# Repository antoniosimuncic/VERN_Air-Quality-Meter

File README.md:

# VERN' University  
Internet of Things Department  
Professor: doc. dr. sc. Petar Kolar, Roman Rubčić, dipl. ing. graf. teh.  
Student: Antonio Šimunčić  

**Smart air quality monitor**  

Zagreb, Croatia  
November, 2024  

# Introduction to the Smart Air Quality Monitor Project

Air pollution is becoming an increasingly serious environmental and health issue, affecting people's quality of life worldwide. Harmful particles and gases in the atmosphere can lead to numerous health problems, making air quality monitoring essential for protecting health and the environment.

The goal of this project is to develop a Smart Air Quality Monitor, a smart meteorological station that integrates advanced sensors to measure airborne dust particles, CO2, humidity, pressure, and temperature. This device would enable real-time air quality monitoring, providing users with critical information to help them make informed decisions and take necessary precautions.

# Week 1 - System architecture

Project Requirements:  

- **Temperature and Humidity Measurement**
- **Dust Particle Measurement** (PM1, PM2.5, PM4, PM10)
- **VOC Index Measurement** (Volatile Organic Compounds)
- **CO2 Level Measurement** in the Air
- **Atmospheric Pressure Measurement**
- **User Data Display**
- **Wireless Network Connectivity**

After defining the device requirements, I began searching for suitable components on platforms like Mouser, TME, and Aliexpress to find those that best match the specifications. The goal was to select reliable components that ensure high accuracy and longevity of the system, while also being compatible with the microcontroller and its software support.

For the microcontroller, I chose the ESP32-S3-WROOM-1 (N16R8) due to its affordable price, dual-core processor, ample onboard flash memory (16MB), and integrated PSRAM (8MB), which serves as a frame buffer for generating the graphical interface. Additionally, the microcontroller module includes built-in Wi-Fi and Bluetooth RF interfaces and an antenna, which significantly shortens development time and reduces the risk of wireless communication issues. 

**Block diagram:**  

# Week 2 - Schematic drawing

In week 2, I began creating the schematic in KiCad. The first task was to place all the selected components in the schematic, followed by a detailed study of the datasheets for the chosen components to ensure correct connections and desired system functionality. At this stage, I am also working on optimizing the schematic and the Bill of Materials (BOM) for a smooth transition to PCB design later on.

# Week 3 - Schematic release

In week 3, I completed the schematic design and released the finalized version. This involved thoroughly verifying all component connections and ensuring compatibility across the system, focusing on power distribution, signal integrity, and communication pathways between components. After careful checks, I created a preliminary Bill of Materials (BOM) and added detailed annotations to the schematic to guide the upcoming PCB layout phase. The release of the schematic marks a significant milestone, setting the foundation for the PCB design and allowing for initial testing.

**Schematic:** [Revision 10](https://github.com/antoniosimuncic/VERN_Air-Quality-Meter/blob/main/Hardware/100008_hw-vern-aqm/Schematic/100008_hw-vern-aqm.pdf)

# Week 4 - PCB design

In the fourth week of the project, I began designing the PCB based on the finalized schematic. This phase involved selecting the appropriate board dimensions, component placement, and routing the connections while considering design rules such as trace width, clearance, and power and heat management. A key focus was on USB differential pair impedance control, ensuring that the USB signal traces were routed with the correct 90Ω differential impedance to maintain signal integrity and reliable data transfer. I also worked on optimizing the layout for signal integrity, minimizing the length of high-speed signal traces, and ensuring proper reference planes and return paths for the components. After completing the layout and routing, I performed a Design Rule Check (DRC) to identify and correct any potential issues before moving on to generating the Gerber files for fabrication.

**PCB render:**  

# Week 5 - Component procurement  

In week 5, I focused on component procurement and ordering essential parts to prepare for assembly. I purchased components from Mouser to ensure the reliability of critical parts while sourcing additional items from Aliexpress for cost-effectiveness. Additionally, I ordered the PCBs and a stencil for solder application from JLCPCB. With components and PCBs on the way, the project is set to progress smoothly into the assembly phase once all parts arrive.

[Bill of Materials](https://html-preview.github.io/?url=https://github.com/antoniosimuncic/VERN_Air-Quality-Meter/blob/main/Hardware/100008_hw-vern-aqm/Manufacturing/Assembly/ibom/ibom.html)  

[Project expense report](https://github.com/antoniosimuncic/VERN_Air-Quality-Meter/blob/main/Documentation/project-expense-report.md)  

# Week 6 - PCB Assembly  

In week 6, I began assembling the PCB as the components and boards had arrived. Using the stencil from JLCPCB, I applied solder paste to the pads, and then I carefully placed each component onto the board, paying special attention to orientation and alignment. After assembling the board, I placed the board on an SMD hotplate reflow soldering station to perform the reflow soldering process. After the board cooled down, I inspected the connections to ensure the soldering process finished successfully. With the PCB assembly complete, I began the first board power-up to do the initial testing and troubleshooting.  

**Production process:**  

# Week 7 - Board Bring-Up  

In week 7, I focused on the initial bring-up of the PCB. After assembling the board, I verified the power rails and ensured all components received the correct voltages. Basic functionality, including communication interfaces such as UART and I2C, was tested to confirm proper connectivity between the microcontroller and peripherals. Rigol DS1054z oscilloscope was used to identify and resolve minor issues on the UART lines. Soldering fixes were necessary to ensure the board operated as expected. This stage established a solid foundation for further firmware development and system testing.  

**Sensor test source code:** [sensors-bring-up.cpp](https://github.com/antoniosimuncic/VERN_Air-Quality-Meter/blob/main/Documentation/sensors-bring-up.cpp)  

# Week 8 - Case design  

In week 8, I focused on designing a custom 3D-printed case for the device after I had confirmed the board functioned as expected. The design accounted for component placement, ventilation, and accessibility for ports and connectors. Aesthetics and durability were considered to ensure the case complemented the functionality and appearance of the project. This step helped prepare the device for practical use and testing in real-world conditions. The 3D print was made using PET-G on the BambuLab P1S printer.  

**Case design:**  

# Week 9: Firmware Architecture and Server Communication

In week 9, the focus was on developing and refining the firmware responsible for Wi-Fi connectivity, data acquisition, and communication with an HTTP server. Below is a detailed breakdown of the tasks completed and code implementations.

### Wi-Fi Connectivity

The firmware establishes a Wi-Fi connection using the ESP32-S3 microcontroller. A robust retry mechanism was implemented to handle connection failures.

**Code Snippet**:
```c
void connectToWifi() {
    uint8_t attempt = 0;
    while (attempt < WIFI_RETRIES) {
        Serial.printf("Attempt %u to connect to Wi-Fi...\n", attempt++);
        WiFi.mode(WIFI_STA);
        WiFi.begin(SECRET_SSID, SECRET_PASSWORD);
        unsigned long startAttemptTime = millis();
        while (WiFi.status() != WL_CONNECTED && millis() - startAttemptTime < WIFI_TIMEOUT) {
            delay(10);
            yield();
        }
        if (WiFi.status() == WL_CONNECTED) {
            Serial.println("Connected to Wi-Fi");
            Serial.print("IP Address: ");
            Serial.println(WiFi.localIP());
            return;
        }
        Serial.println("Failed to connect. Retrying...");
        delay(2000);
        attempt++;
    }
    Serial.println("Exceeded maximum retry attempts. Check your Wi-Fi credentials or network.");
}
```

### Server Communication

Data collected from sensors is sent to an HTTP server in JSON format. The sendDataToHTTPServer function handles this process, including constructing the JSON payload and managing HTTP requests.

**Request body:**
```json
{
 "mac_address": "AA:BB:CC:DD:EE:FF",
 "temperature": 22.5,
 "humidity": 45.0,
 "pm1": 10,
 "pm2_5": 20,
 "pm4": 25,
 "pm10": 30,
 "co2": 450,
 "voc": 100,
 "pressure": 1013.25
}
```
     
**Code Snippet:**
```c
void sendDataToHTTPServer(String mac_address, float temperature, float humidity, float pm1, float pm2_5, float pm4, float pm10, uint16_t co2, float voc, float pressure) {
    String jsonData = "{";
    jsonData += "\"mac_address\":\"" + mac_address + "\",";
    jsonData += "\"temperature\":" + String(temperature) + ",";
    jsonData += "\"humidity\":" + String(humidity) + ",";
    jsonData += "\"pm1\":" + String(pm1) + ",";
    jsonData += "\"pm2_5\":" + String(pm2_5) + ",";
    jsonData += "\"pm4\":" + String(pm4) + ",";
    jsonData += "\"pm10\":" + String(pm10) + ",";
    jsonData += "\"co2\":" + String(co2) + ",";
    jsonData += "\"voc\":" + String(voc) + ",";
    jsonData += "\"pressure\":" + String(pressure);
    jsonData += "}";

    if (WiFi.status() == WL_CONNECTED) {
        HTTPClient http;
        http.begin(SERVER_URL);
        http.addHeader("Content-Type", "application/json");
        int httpResponseCode = http.POST(jsonData);
        if (httpResponseCode > 0) {
            String response = http.getString();
            Serial.println("Response code: " + String(httpResponseCode));
            Serial.println("Response: " + response);
        } else {
            Serial.println("Error on sending POST: " + String(httpResponseCode));
        }
        http.end();
    } else {
        Serial.println("Wi-Fi not connected");
    }
}
```
**View Full Code:** [server_functions.cpp](https://github.com/antoniosimuncic/VERN_Air-Quality-Meter/blob/main/Software/100009-fw-vern-aqm/lib/server_functions/server_functions.cpp)

# Week 10: LCD Integration and Sensor Visualization

In week 10, the focus shifted to integrating the TFT display for visualizing sensor data. The firmware includes functionality for determining display colors based on sensor values, enhancing user experience.

### Dynamic Value Coloring

Each sensor value is displayed in a color-coded format to indicate its status (e.g., good, mediocre, bad, terrible).  
Functions like `getTempColor()` and `getHumidityColor()` determine the appropriate color for each value.

**Code Snippet:**
```c
uint16_t getHumidityColor(float humidity) {

    uint8_t targetHumidity = 50;
    if (abs(targetHumidity-humidity) <= 10) {
        return GOOD_COLOR;  // Green for humidity 40-60%
    } else if (abs(targetHumidity-humidity) <= 15) {
        return MEDIOCRE_COLOR;  // Yellow for humidity 35-65%
    } else if (abs(targetHumidity-humidity) <= 20) {
        return BAD_COLOR;  // Orange for humidity 30-70%
    } else {
        return TERRIBLE_COLOR;  // Red for humidity under 30 or over 70%
    }
}
```
**View Full Code:** [lcd_functions.cpp](https://github.com/antoniosimuncic/VERN_Air-Quality-Meter/blob/main/Software/100009-fw-vern-aqm/lib/lcd_functions/lcd_functions.cpp)

### Sensor Value Visualization

The display shows sensor values for temperature, humidity, CO2, VOC Index, and particulate matter (PM1, PM2.5, PM10). Each value is updated dynamically and rendered in real time.

**Code Snippet:**
```c
// Draw initial UI with Wi-Fi credentials
void drawUI() {
    sprite.fillSprite(BACKGROUND_COLOR);

    drawClockAndWiFi();

    sprite.setTextDatum(TL_DATUM); // Top-left
    sprite.setTextColor(TEXT_COLOR, TOP_BAR_COLOR);
    sprite.setTextSize(3);
    sprite.drawString("Time Zone", 10, 8);
    sprite.setTextDatum(TL_DATUM); // Top-left
    sprite.setTextColor(TEXT_COLOR, BACKGROUND_COLOR);
    sprite.setTextSize(3);
    sprite.drawString("SSID:", 20, 60);  sprite.drawString(SECRET_SSID, 120, 60);
    sprite.drawString("PASS:", 20, 120); sprite.drawString(SECRET_PASSWORD, 120, 120);
    sprite.drawString("IP:", 20, 180); sprite.drawString(ipString, 120, 180);

    sprite.pushSprite(0, 0);
    sprite.fillRect(0,35,480,285, BACKGROUND_COLOR);
    sprite.pushSprite(0, 0);

}

// Draw widgets with specified values
void drawWidget(int x, int y, int w, int h, const char* label, const char* unit, const char* value, uint16_t color) {
    // Draw the rounded rectangle
    sprite.fillRoundRect(x, y, w, h, 10, color);
    sprite.fillRoundRect(x + 5, y + 5, w - 10, h - 10, 5, BACKGROUND_COLOR);

    // Draw the label
    sprite.setTextColor(TEXT_COLOR, BACKGROUND_COLOR);
    sprite.setTextDatum(TC_DATUM);
    sprite.setTextSize(2);
    sprite.drawString(label, x + w / 2, y + 12);

    // Draw the value
    sprite.setTextSize(2);
    sprite.setTextColor(MEASUREMENT_TEXT_COLOR, BACKGROUND_COLOR);
    sprite.drawString(value, x + w / 2, (y + h / 2)-10);

    // Draw the measurement unit
    sprite.setTextColor(TEXT_COLOR, BACKGROUND_COLOR);
    sprite.setTextDatum(TC_DATUM);
    sprite.setTextSize(2);
    sprite.drawString(unit, x + w / 2, y + 80);
}

// Update each widget with new sensor values
void updateUI() {
    uint8_t x = 3;
    uint8_t y = 55;
    uint8_t w = 110;
    uint8_t h = 110;
    uint8_t v_space = 25;

    drawWidget(x +   0, y, w, h, "Temp",     "C",   String(TEMPERATURE, 1).c_str(),  getTempColor(TEMPERATURE));
    drawWidget(x + 120, y, w, h, "RH",       "%",   String(HUMIDITY, 1).c_str(),     getHumidityColor(HUMIDITY));
    drawWidget(x + 240, y, w, h, "CO2",      "ppm", String(CO2).c_str(),             getCO2Color(CO2));
    drawWidget(x + 360, y, w, h, "Pressure", "hPa", String(PRESSURE/100, 2).c_str(), getPressureColor(PRESSURE));

    drawWidget(x +   0, y + h + v_space, w, h, "VOC",   "Index", String(VOC_INDEX, 0).c_str(), getVOCColor(VOC_INDEX));
    drawWidget(x + 120, y + h + v_space, w, h, "PM1",   "ug/m3", String(PM1, 0).c_str(),       getPM1Color(PM1));
    drawWidget(x + 240, y + h + v_space, w, h, "PM2.5", "ug/m3", String(PM2_5, 0).c_str(),     getPM2_5Color(PM2_5));
    drawWidget(x + 360, y + h + v_space, w, h, "PM10",  "ug/m3", String(PM10, 0).c_str(),      getPM10Color(PM10));

    drawClockAndWiFi();

    sprite.pushSprite(0, 0);
}
```
### Time and Wi-Fi indicator  

The top bar of the display is reserved for a digital clock that syncs with a NTP time server on the Wi-Fi network, there is also a red/green dot in the upper right corner that shows Wi-Fi status.

```c
// Draw clock and Wi-Fi indicator
void drawClockAndWiFi() {
    // Draw clock
    unsigned long currentEpoch = timeClient.getEpochTime();
    String currentTime = epochToHoursMinutes(currentEpoch);

    sprite.fillRect(0,0,480,35, TOP_BAR_COLOR);
    sprite.setTextDatum(TC_DATUM); // Top-center
    sprite.setTextColor(TEXT_COLOR, TOP_BAR_COLOR);
    sprite.setTextSize(3);
    sprite.drawString(currentTime, 240, 8);

    // Draw WiFi symbol and indication
    if (WiFi.status() == WL_CONNECTED) {
        sprite.fillCircle(455, 18, 7, TFT_GREEN); // Indicate WiFi connection (green dot)
    } else {
        sprite.fillCircle(455, 18, 7, TFT_RED); // Indicate NO WiFi connection (red dot)
    }
}
```
**View Full Code:** [main.cpp](https://github.com/antoniosimuncic/VERN_Air-Quality-Meter/blob/main/Software/100009-fw-vern-aqm/src/main.cpp)

# Week 11 and 12: Node.js Server with visual data dashboard

Last part of the project was to design a web-application for managing the sensors and viewing and storing the data.  

**Web-App Repository**: [Nodejs-IoT-Server](https://github.com/antoniosimuncic/nodejs-iot-server)  

---

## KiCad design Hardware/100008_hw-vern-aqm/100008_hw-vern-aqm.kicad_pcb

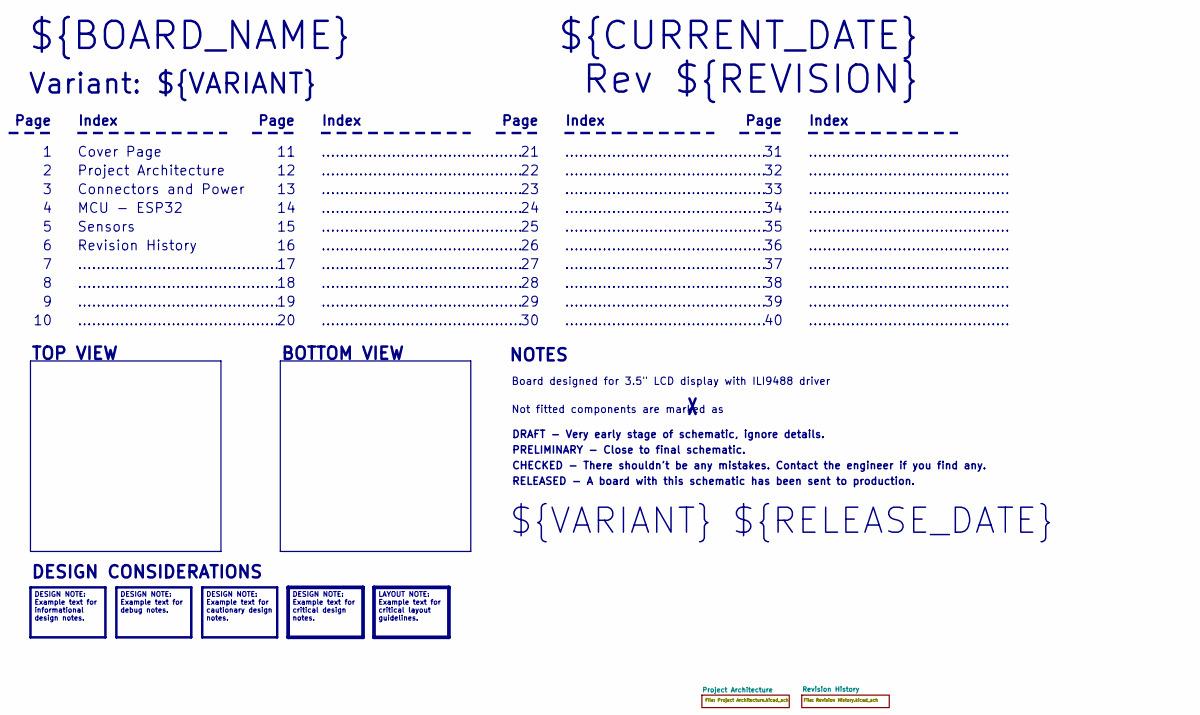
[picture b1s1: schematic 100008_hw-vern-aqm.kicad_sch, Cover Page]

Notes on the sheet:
DESIGN NOTE: Example text for informational design notes.
LAYOUT NOTE: Example text for critical layout guidelines.
DESIGN NOTE: Example text for cautionary design notes.
DESIGN NOTE: Example text for debug notes.
DESIGN NOTE: Example text for critical design notes.
BOTTOM VIEW
...........................................
RELEASED - A board with this schematic has been sent to production.
Page
TOP VIEW
Not fitted components are marked as
Index
PRELIMINARY - Close to final schematic.
${VARIANT} ${RELEASE_DATE}
Connectors and Power
Board designed for 3.5" LCD display with ILI9488 driver
${CURRENT_DATE}
Variant: ${VARIANT}
Rev ${REVISION}
MCU - ESP32
${BOARD_NAME}
DRAFT - Very early stage of schematic, ignore details.
Sensors
Project Architecture
Cover Page
NOTES
CHECKED - There shouldn't be any mistakes. Contact the engineer if you find any.
DESIGN CONSIDERATIONS
Revision History

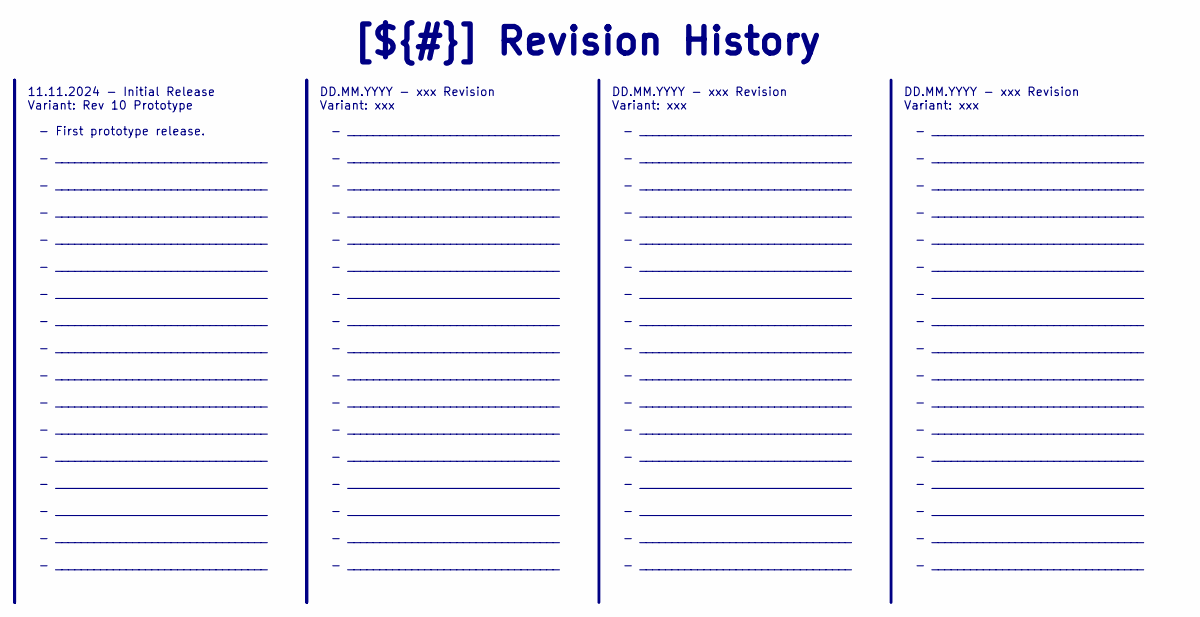
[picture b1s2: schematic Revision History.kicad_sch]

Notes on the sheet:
- _________________________________ - _________________________________ - _________________________________ - _________________________________ - _________________________________ - _________________________________ - _________________________________ - _________________________________ - _________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
DD.MM.YYYY - xxx Revision Variant: xxx
[${#}] ${TITLE}
- First prototype release. - _________________________________ - _________________________________ - _________________________________ - _________________________________ - _________________________________ - _________________________________ - _________________________________ - __________________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
11.11.2024 - Initial Release Variant: Rev 10 Prototype

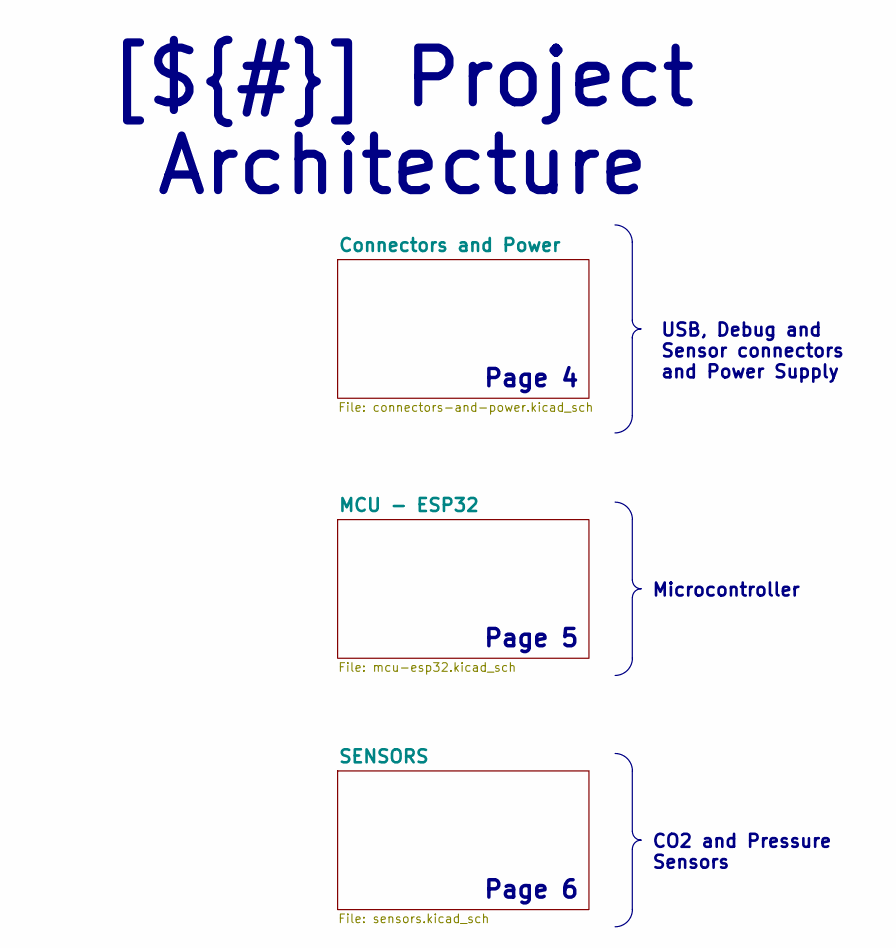
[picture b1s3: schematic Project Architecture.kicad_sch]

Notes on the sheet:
USB, Debug and Sensor connectors and Power Supply
[${#}] ${TITLE}
CO2 and Pressure Sensors
Microcontroller
Page 6
Page 4
Page 5

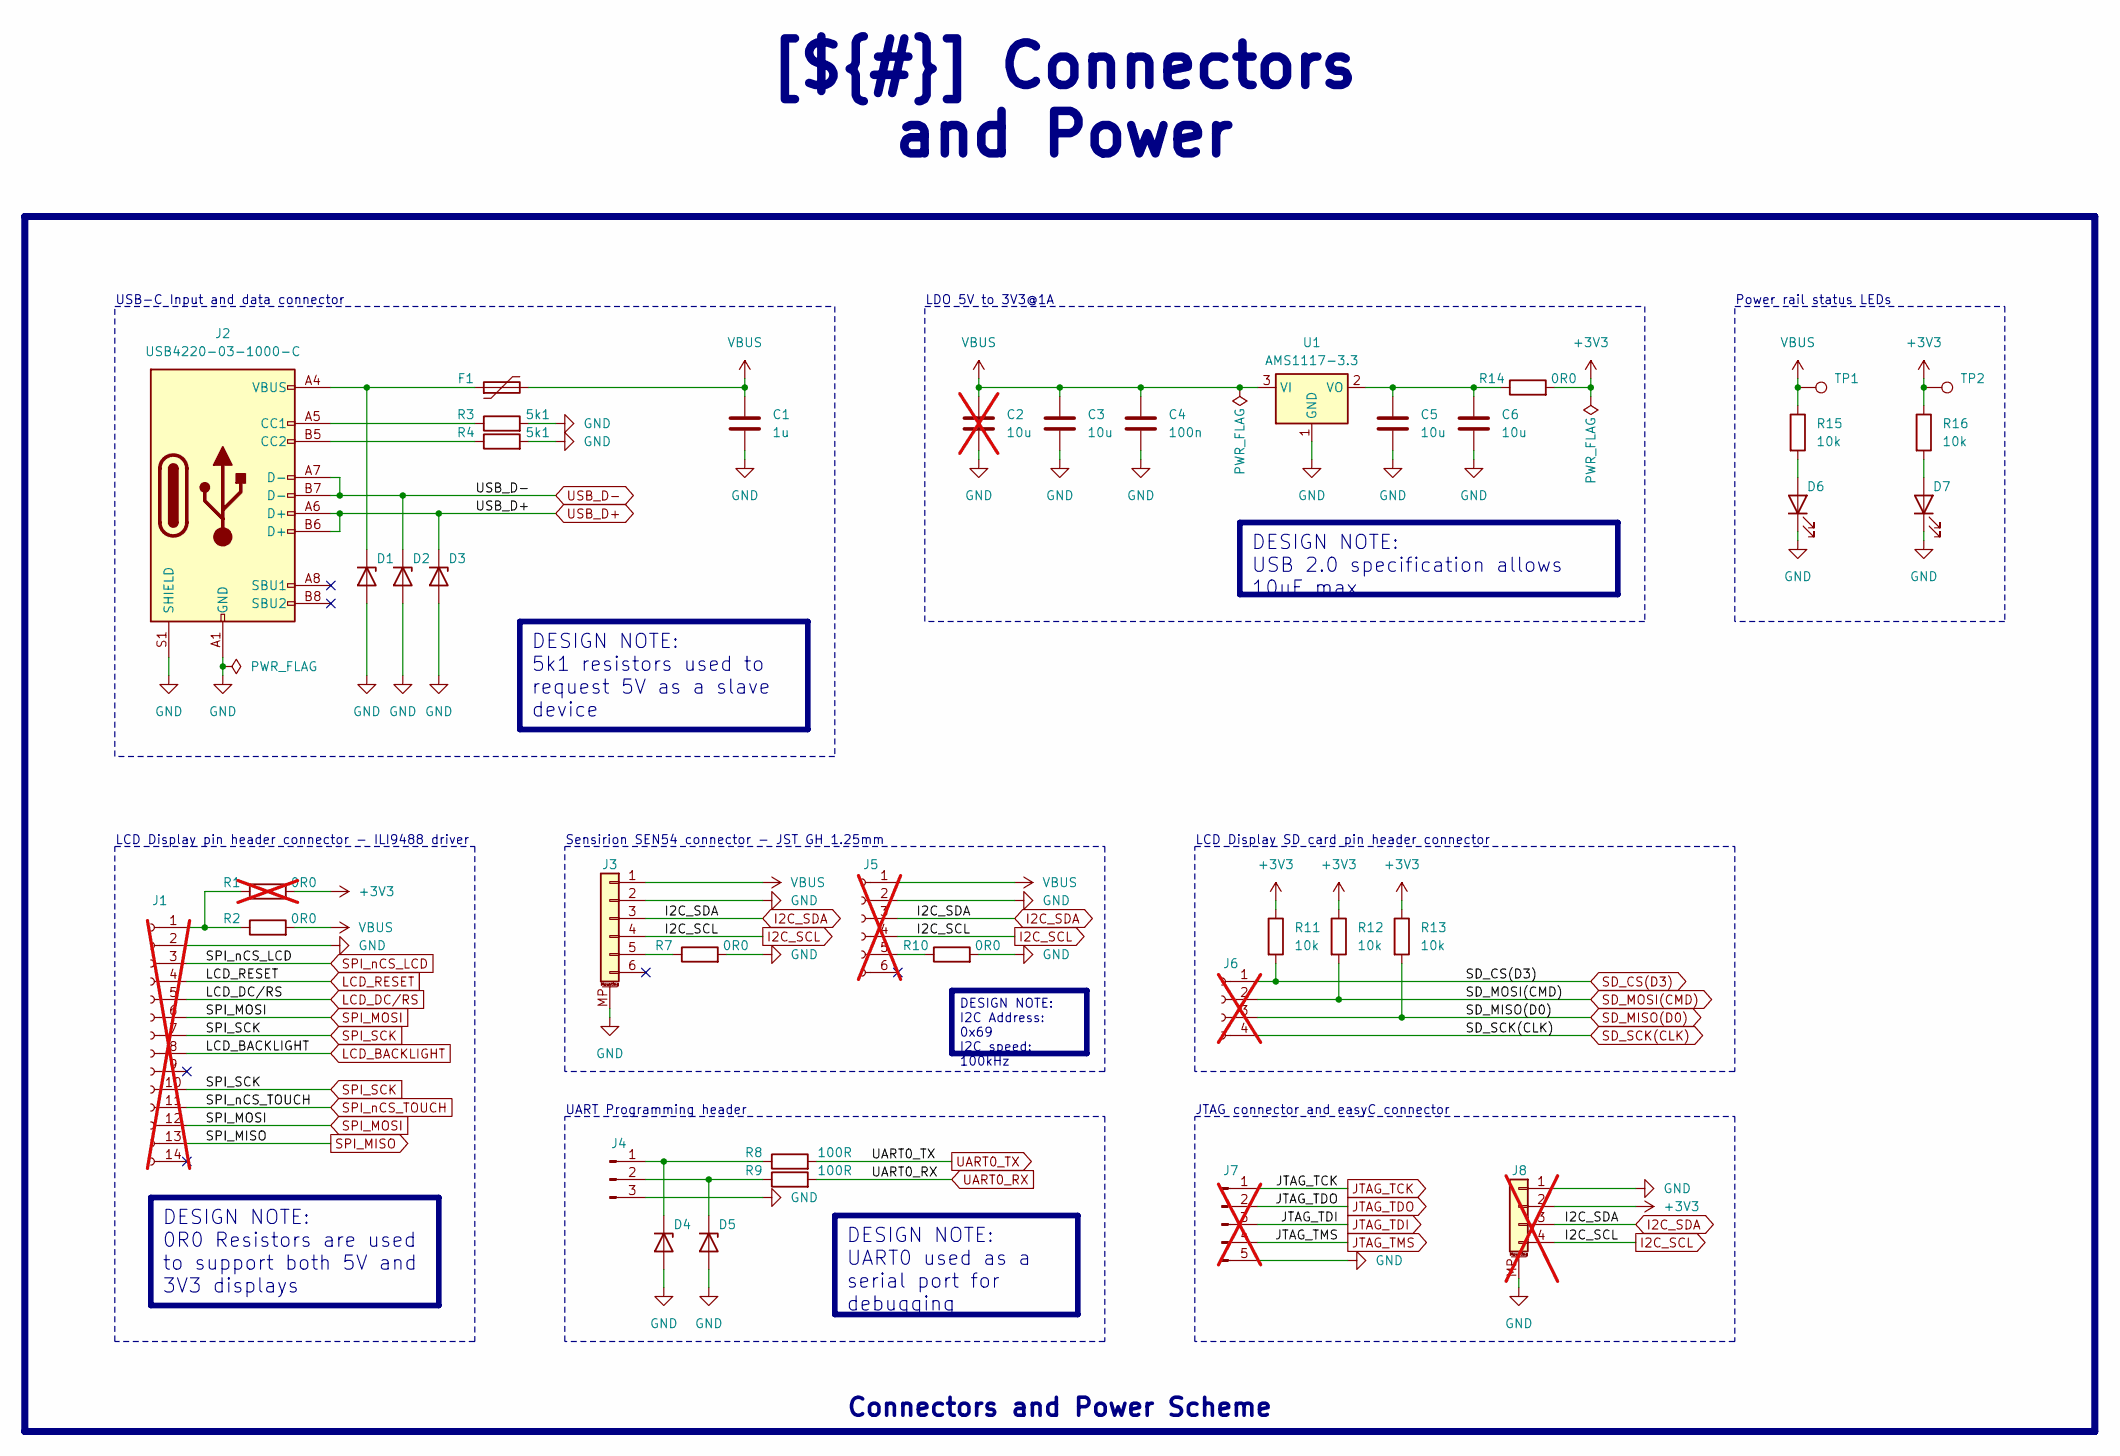
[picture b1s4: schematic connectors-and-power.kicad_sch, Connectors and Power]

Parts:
C1: 1u; C_0805_2012Metric
C2: 10u; C_0805_2012Metric; not fitted
C3, C5, C6: 10u; C_0805_2012Metric
C4: 100n; C_0603_1608Metric
D1: ESD5Z3V3; D_SOD-523
D2, D3, D4, D5: ESD321DYAR; D_SOD-523
D6, D7: LED; LED_0603_1608Metric
F1: Polyfuse; Fuse_1206_3216Metric
J1: Conn_01x14_Socket; PinHeader_1x14_P2.54mm_Vertical; not fitted
J2: USB4220-03-1000-C; USB_C_Receptacle_GCT_USB4220-03-xxxx-C_Vertical
J3: Conn_01x06_MountingPin; JST_GH_BM06B-GHS-TBT_1x06-1MP_P1.25mm_Vertical
J4: Conn_01x03_Pin; PinHeader_1x03_P2.54mm_Vertical
J5: Conn_01x06_Socket; PinHeader_1x06_P2.00mm_Vertical; not fitted
J6: Conn_01x04_Socket; PinHeader_1x04_P2.54mm_Vertical; not fitted
J7: Conn_01x05_Pin; PinHeader_1x05_P2.54mm_Vertical; not fitted
J8: Conn_01x04_MountingPin; JST_SH_SM04B-SRSS-TB_1x04-1MP_P1.00mm_Horizontal; not fitted
R1: 0R0; R_0603_1608Metric; not fitted
R2, R7, R10, R14: 0R0; R_0603_1608Metric
R3, R4: 5k1; R_0603_1608Metric
R8, R9: 100R; R_0603_1608Metric
R11, R12, R13, R15, R16: 10k; R_0603_1608Metric
TP1, TP2: TestPoint; TestPoint_Pad_D1.5mm
U1: AMS1117-3.3; SOT-223-3_TabPin2

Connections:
+3V3: J8.2, R1.2, R11.1, R12.1, R13.1, R14.2, R16.1, TP2.1; also elsewhere on the board
GND: C1.2, C2.2, C3.2, C4.2, C5.2, C6.2, D1.2 (A), D2.2 (A), D3.2 (A), D4.2 (A), D5.2 (A), D6.1 (K), D7.1 (K), J1.2, J2.A1 (GND), J2.A12 (GND), J2.B1 (GND), J2.B12 (GND), J2.S1 (SHIELD), J3.2, J3.MP (MountPin), J4.3, J5.2, J7.5, J8.1, J8.MP (MountPin), R3.2, R4.2, R7.2, R10.2, U1.1 (GND); also elsewhere on the board
I2C_SCL: J3.4, J5.4, J8.4; also elsewhere on the board
I2C_SDA: J3.3, J5.3, J8.3; also elsewhere on the board
JTAG_TCK: J7.1; also elsewhere on the board
JTAG_TDI: J7.3; also elsewhere on the board
JTAG_TDO: J7.2; also elsewhere on the board
JTAG_TMS: J7.4; also elsewhere on the board
LCD_BACKLIGHT: J1.8; also elsewhere on the board
LCD_DC/RS: J1.5; also elsewhere on the board
LCD_RESET: J1.4; also elsewhere on the board
unnamed: D1.1 (K), F1.1, J2.A4 (VBUS), J2.A9 (VBUS), J2.B4 (VBUS), J2.B9 (VBUS)
unnamed: D4.1 (K), J4.1, R8.1
unnamed: D5.1 (K), J4.2, R9.1
unnamed: D6.2 (A), R15.2
unnamed: D7.2 (A), R16.2
unnamed: J1.1, R1.1, R2.1
unnamed: J2.A5 (CC1), R3.1
unnamed: J2.B5 (CC2), R4.1
unnamed: J3.5, R7.1
unnamed: J5.5, R10.1
unnamed: C5.1, C6.1, R14.1, U1.2 (VO)
SD_CS(D3): J6.1, R11.2; also elsewhere on the board
SD_MISO(D0): J6.3, R13.2; also elsewhere on the board
SD_MOSI(CMD): J6.2, R12.2; also elsewhere on the board
SD_SCK(CLK): J6.4; also elsewhere on the board
SPI_MISO: J1.13; also elsewhere on the board
SPI_MOSI: J1.6, J1.12; also elsewhere on the board
SPI_SCK: J1.7, J1.10; also elsewhere on the board
SPI_nCS_LCD: J1.3; also elsewhere on the board
SPI_nCS_TOUCH: J1.11; also elsewhere on the board
UART0_RX: R9.2; also elsewhere on the board
UART0_TX: R8.2; also elsewhere on the board
USB_D+: D3.1 (K), J2.A6 (D+), J2.B6 (D+); also elsewhere on the board
USB_D-: D2.1 (K), J2.A7 (D-), J2.B7 (D-); also elsewhere on the board
VBUS: C1.1, C2.1, C3.1, C4.1, F1.2, J3.1, J5.1, R2.2, R15.1, TP1.1, U1.3 (VI); also elsewhere on the board

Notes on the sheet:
DESIGN NOTE: USB 2.0 specification allows 10uF max.
DESIGN NOTE: 5k1 resistors used to request 5V as a slave device
DESIGN NOTE: 0R0 Resistors are used to support both 5V and 3V3 displays
DESIGN NOTE: UART0 used as a serial port for debugging
[${#}] ${TITLE}
Connectors and Power Scheme
DESIGN NOTE: I2C Address: 0x69 I2C speed: 100kHz
Power rail status LEDs
LCD Display SD card pin header connector
Sensirion SEN54 connector - JST GH 1.25mm
JTAG connector and easyC connector
UART Programming header
LCD Display pin header connector - ILI9488 driver
LDO 5V to 3V3@1A
USB-C Input and data connector

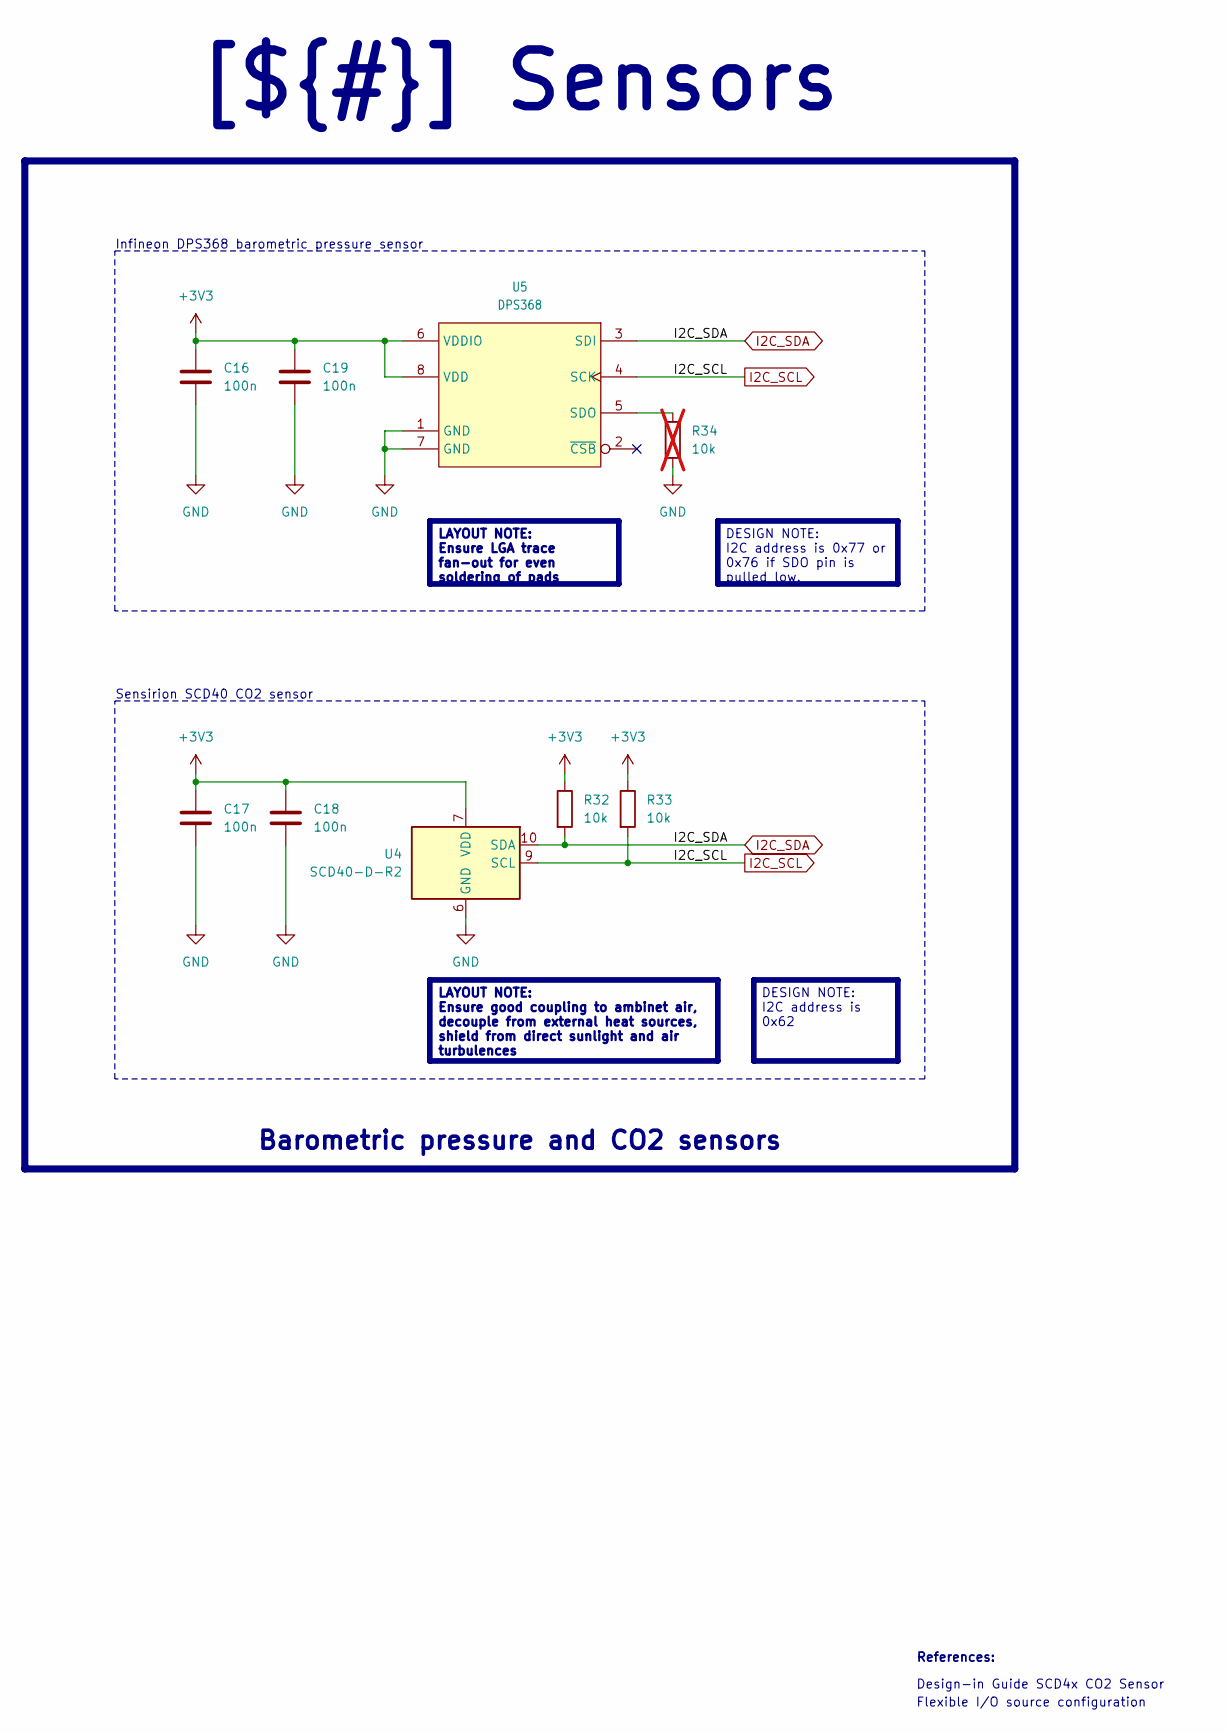
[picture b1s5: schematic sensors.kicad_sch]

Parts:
C16, C17, C18, C19: 100n; C_0603_1608Metric
R32, R33: 10k; R_0603_1608Metric
R34: 10k; R_0603_1608Metric; not fitted
U4: SCD40-D-R2; Sensirion_SCD4x-1EP_10.1x10.1mm_P1.25mm_EP4.8x4.8mm
U5: DPS368; LGA8S145X65P2X4_200X250X110-V

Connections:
+3V3: C16.1, C17.1, C18.1, C19.1, R32.1, R33.1, U4.7 (VDD), U4.19 (VDD), U5.6 (VDDIO), U5.8 (VDD); also elsewhere on the board
GND: C16.2, C17.2, C18.2, C19.2, R34.2, U4.6 (GND), U4.20 (GND), U4.21 (GND), U5.1 (GND), U5.7 (GND); also elsewhere on the board
I2C_SCL: R33.2, U4.9 (SCL), U5.4 (SCK); also elsewhere on the board
I2C_SDA: R32.2, U4.10 (SDA), U5.3 (SDI); also elsewhere on the board
unnamed: R34.1, U5.5 (SDO)

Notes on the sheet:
[${#}] ${TITLE}
LAYOUT NOTE: Ensure good coupling to ambinet air, decouple from external heat sources, shield from direct sunlight and air turbulences
LAYOUT NOTE: Ensure LGA trace fan-out for even soldering of pads
Barometric pressure and CO2 sensors
DESIGN NOTE: I2C address is 0x62
DESIGN NOTE: I2C address is 0x77 or 0x76 if SDO pin is pulled low.
Design-in Guide SCD4x CO2 Sensor
Infineon DPS368 barometric pressure sensor
Sensirion SCD40 CO2 sensor
References:
Flexible I/O source configuration

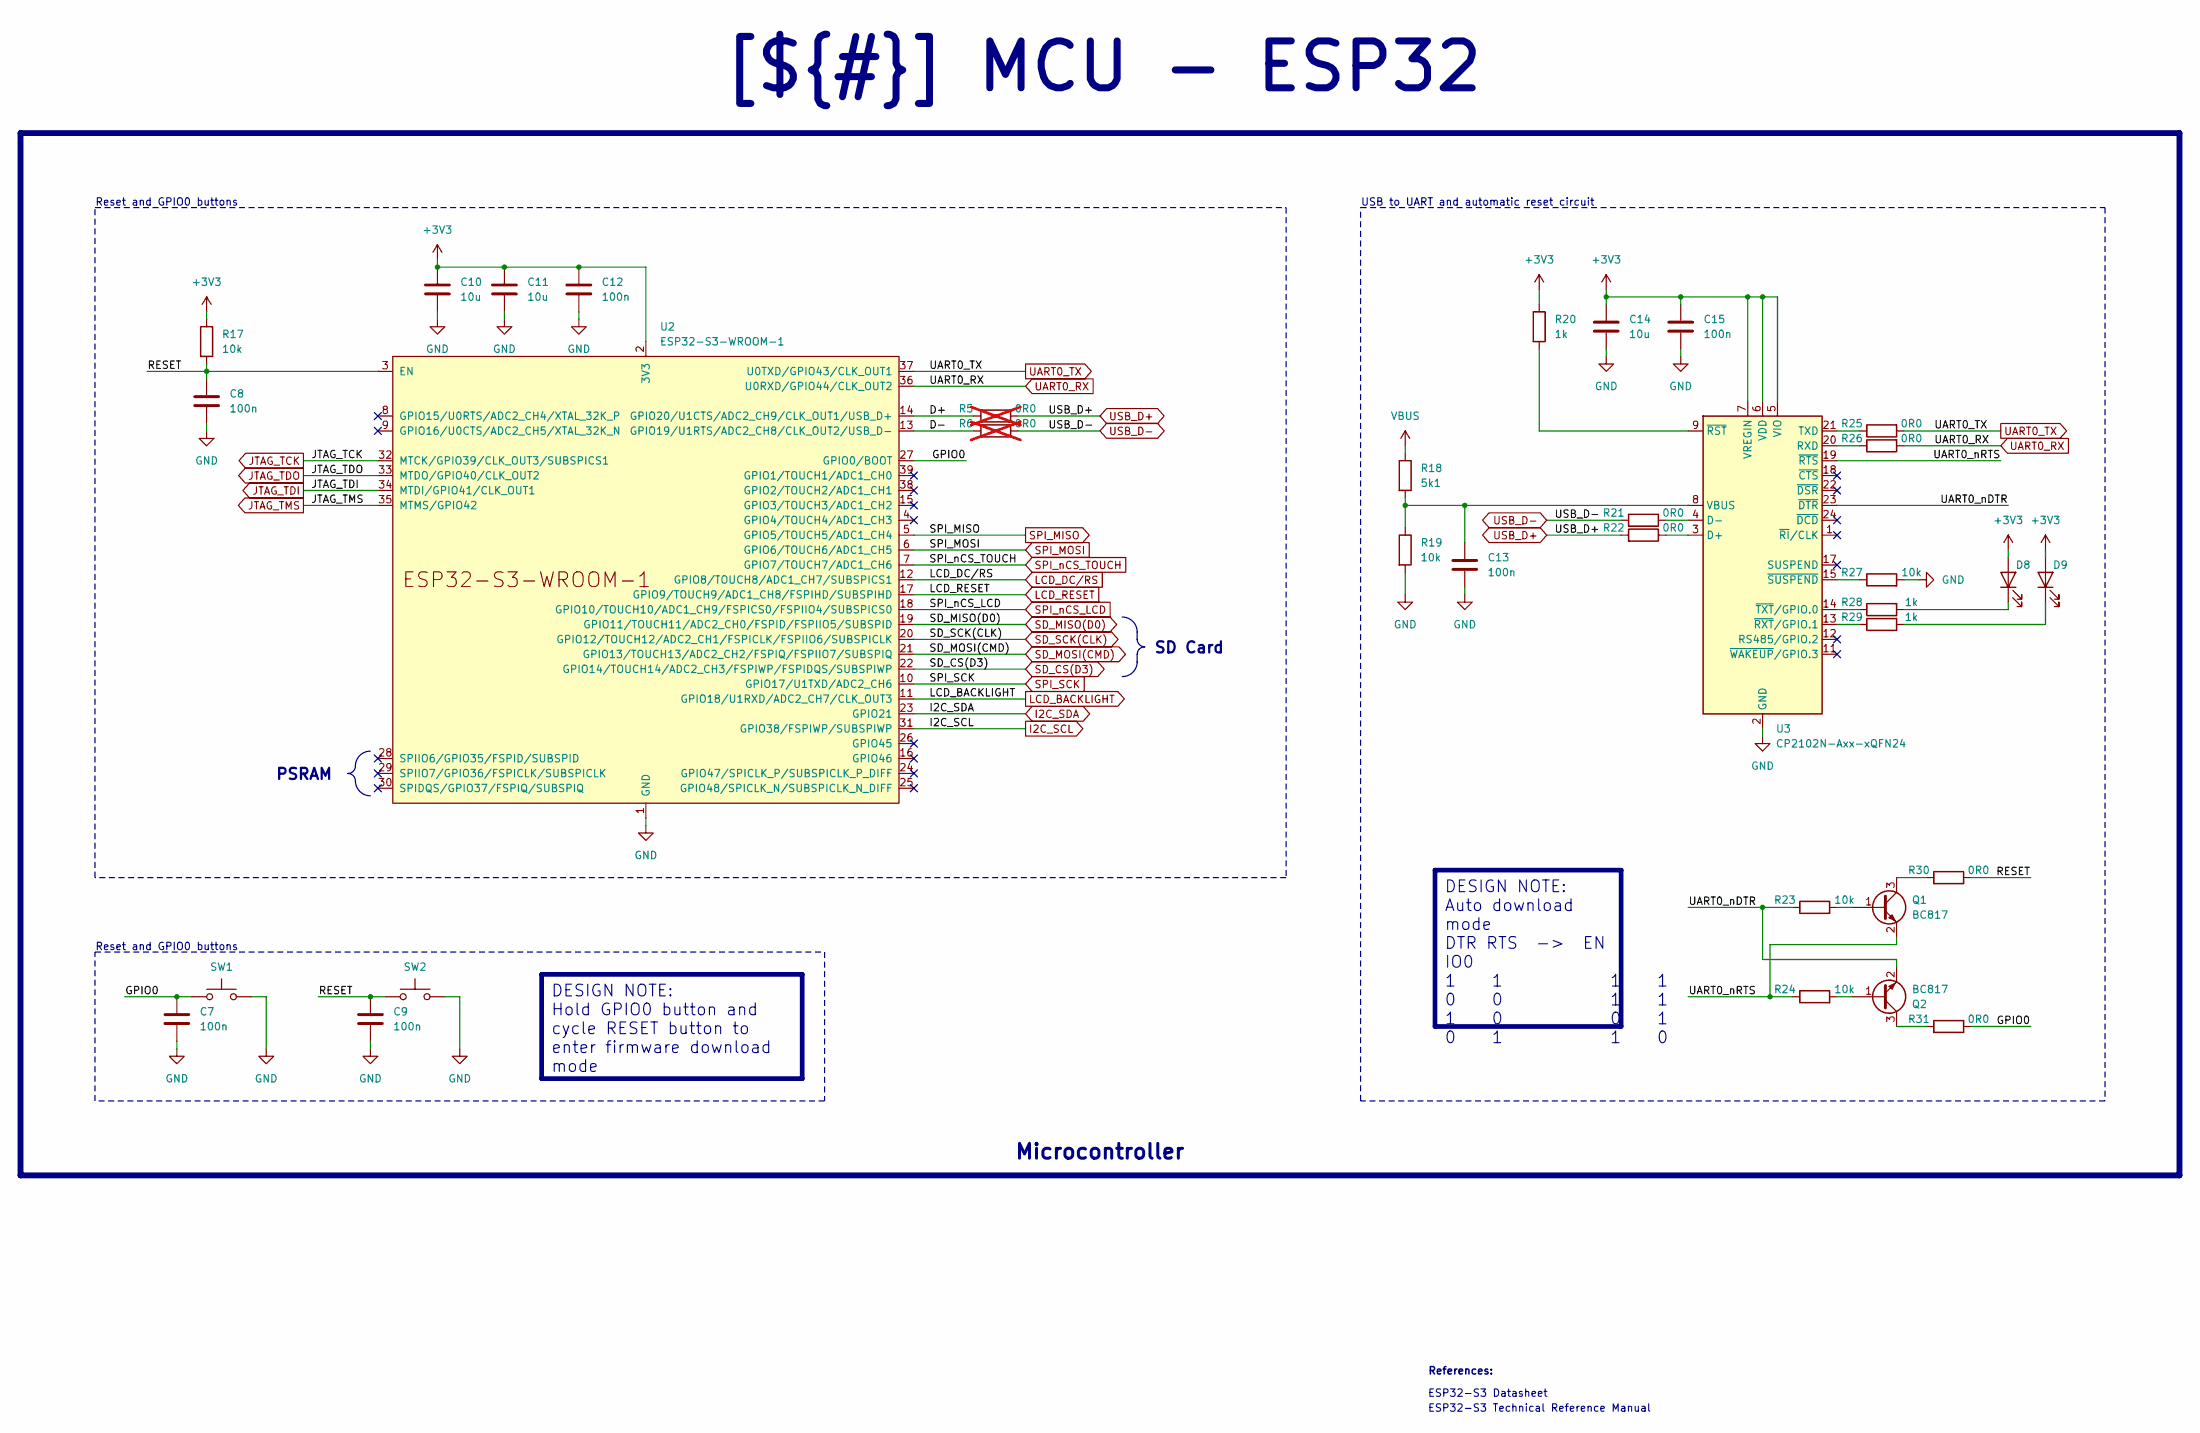
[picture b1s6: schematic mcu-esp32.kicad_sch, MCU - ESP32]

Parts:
C7, C8, C9, C12, C13, C15: 100n; C_0603_1608Metric
C10, C11, C14: 10u; C_0805_2012Metric
D8, D9: LED; LED_0603_1608Metric
Q1, Q2: BC817; SOT-323_SC-70
R5, R6: 0R0; R_0603_1608Metric; not fitted
R17, R19, R23, R24, R27: 10k; R_0603_1608Metric
R18: 5k1; R_0603_1608Metric
R20, R28, R29: 1k; R_0603_1608Metric
R21, R22, R25, R26, R30, R31: 0R0; R_0603_1608Metric
SW1, SW2: SW_Push; SW_Tactile_SPST_NO_Straight_CK_PTS636Sx25SMTRLFS
U2: ESP32-S3-WROOM-1
U3: CP2102N-Axx-xQFN24; QFN-24-1EP_4x4mm_P0.5mm_EP2.6x2.6mm

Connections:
+3V3: C10.1, C11.1, C12.1, C14.1, C15.1, D8.2 (A), D9.2 (A), R17.1, R20.1, U2.2 (3V3), U3.5 (VIO), U3.6 (VDD), U3.7 (VREGIN); also elsewhere on the board
/Project Architecture/MCU - ESP32/D+: R5.2, U2.14 (GPIO20/U1CTS/ADC2_CH9/CLK_OUT1/USB_D+)
/Project Architecture/MCU - ESP32/D-: R6.2, U2.13 (GPIO19/U1RTS/ADC2_CH8/CLK_OUT2/USB_D-)
/Project Architecture/MCU - ESP32/GPIO0: C7.1, R31.1, SW1.1, U2.27 (GPIO0/BOOT)
/Project Architecture/MCU - ESP32/RESET: C8.1, C9.1, R17.2, R30.1, SW2.1, U2.3 (EN)
/Project Architecture/MCU - ESP32/UART0_nDTR: Q2.2 (E), R23.1, U3.23 (~DTR)
/Project Architecture/MCU - ESP32/UART0_nRTS: Q1.2 (E), R24.1, U3.19 (~RTS)
GND: C7.2, C8.2, C9.2, C10.2, C11.2, C12.2, C13.2, C14.2, C15.2, R19.2, R27.2, SW1.2, SW2.2, U2.1 (GND), U2.40 (GND), U2.41 (GND), U3.2 (GND), U3.25 (GND); also elsewhere on the board
I2C_SCL: U2.31 (GPIO38/FSPIWP/SUBSPIWP); also elsewhere on the board
I2C_SDA: U2.23 (GPIO21); also elsewhere on the board
JTAG_TCK: U2.32 (MTCK/GPIO39/CLK_OUT3/SUBSPICS1); also elsewhere on the board
JTAG_TDI: U2.34 (MTDI/GPIO41/CLK_OUT1); also elsewhere on the board
JTAG_TDO: U2.33 (MTDO/GPIO40/CLK_OUT2); also elsewhere on the board
JTAG_TMS: U2.35 (MTMS/GPIO42); also elsewhere on the board
LCD_BACKLIGHT: U2.11 (GPIO18/U1RXD/ADC2_CH7/CLK_OUT3); also elsewhere on the board
LCD_DC/RS: U2.12 (GPIO8/TOUCH8/ADC1_CH7/SUBSPICS1); also elsewhere on the board
LCD_RESET: U2.17 (GPIO9/TOUCH9/ADC1_CH8/FSPIHD/SUBSPIHD); also elsewhere on the board
unnamed: D8.1 (K), R28.2
unnamed: D9.1 (K), R29.2
unnamed: Q1.1 (B), R23.2
unnamed: Q1.3 (C), R30.2
unnamed: Q2.1 (B), R24.2
unnamed: Q2.3 (C), R31.2
unnamed: R22.1, U3.3 (D+)
unnamed: R21.1, U3.4 (D-)
unnamed: R26.1, U3.20 (RXD)
unnamed: R25.1, U3.21 (TXD)
unnamed: C13.1, R18.2, R19.1, U3.8 (VBUS)
unnamed: R20.2, U3.9 (~RST)
unnamed: R29.1, U3.13 (~RXT/GPIO.1)
unnamed: R27.1, U3.15 (~SUSPEND)
unnamed: R28.1, U3.14 (~TXT/GPIO.0)
SD_CS(D3): U2.22 (GPIO14/TOUCH14/ADC2_CH3/FSPIWP/FSPIDQS/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); also elsewhere on the board
SD_MISO(D0): U2.19 (GPIO11/TOUCH11/ADC2_CH0/FSPID/FSPIIO5/S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); also elsewhere on the board
SD_MOSI(CMD): U2.21 (GPIO13/TOUCH13/ADC2_CH2/FSPIQ/FSPIIO7/S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); also elsewhere on the board
SD_SCK(CLK): U2.20 (GPIO12/TOUCH12/ADC2_CH1/FSPICLK/FSPIIO6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); also elsewhere on the board
SPI_MISO: U2.5 (GPIO5/TOUCH5/ADC1_CH4); also elsewhere on the board
SPI_MOSI: U2.6 (GPIO6/TOUCH6/ADC1_CH5); also elsewhere on the board
SPI_SCK: U2.10 (GPIO17/U1TXD/ADC2_CH6); also elsewhere on the board
SPI_nCS_LCD: U2.18 (GPIO10/TOUCH10/ADC1_CH9/FSPICS0/FSPIIO4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); also elsewhere on the board
SPI_nCS_TOUCH: U2.7 (GPIO7/TOUCH7/ADC1_CH6); also elsewhere on the board
UART0_RX: R26.2, U2.36 (U0RXD/GPIO44/CLK_OUT2); also elsewhere on the board
UART0_TX: R25.2, U2.37 (U0TXD/GPIO43/CLK_OUT1); also elsewhere on the board
USB_D+: R5.1, R22.2; also elsewhere on the board
USB_D-: R6.1, R21.2; also elsewhere on the board
VBUS: R18.1; also elsewhere on the board

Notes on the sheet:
DESIGN NOTE: Auto download mode DTR RTS -> EN IO0 1 1 1 1 0 0 1 1 1 0 0 1 0 1 1 0
DESIGN NOTE: Hold GPIO0 button and cycle RESET button to enter firmware download mode
[${#}] ${TITLE}
SD Card
PSRAM
Microcontroller
Reset and GPIO0 buttons
ESP32-S3 Datasheet
USB to UART and automatic reset circuit
References:
ESP32-S3 Technical Reference Manual

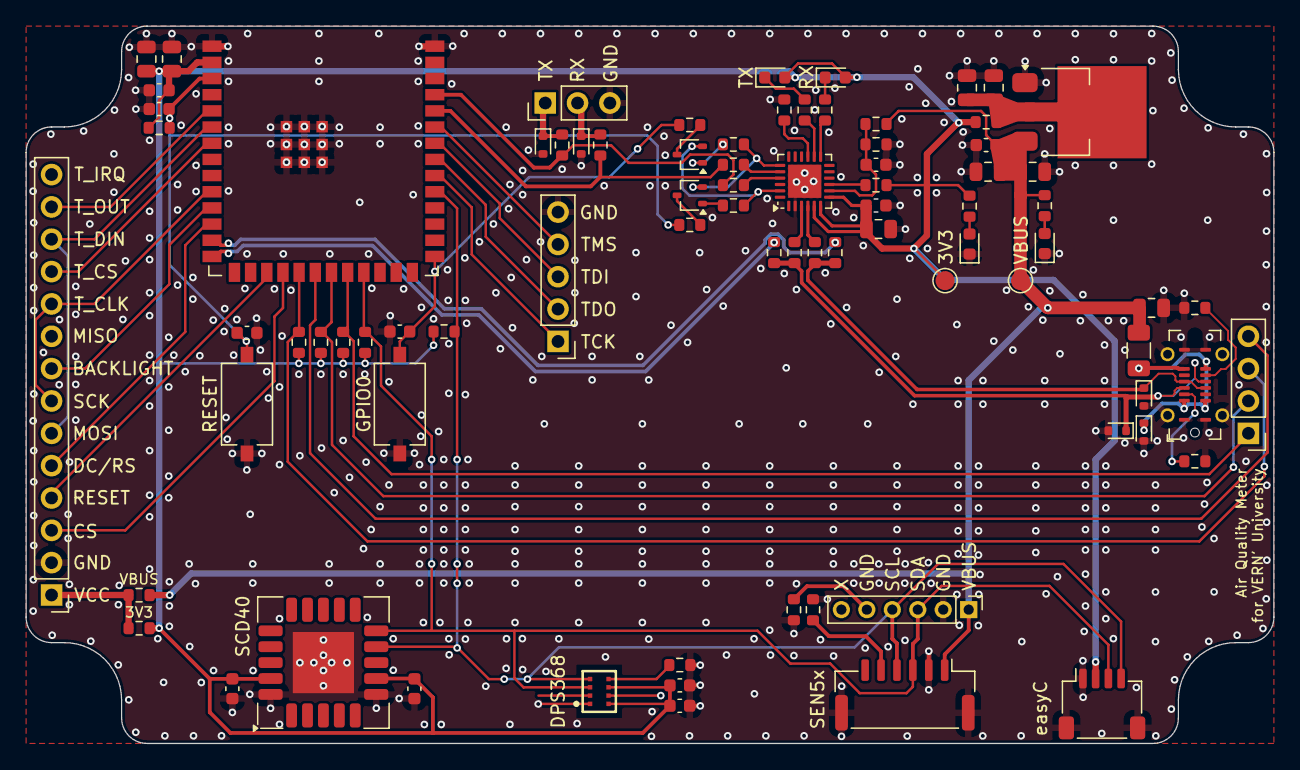
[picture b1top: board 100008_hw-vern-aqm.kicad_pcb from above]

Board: 4 copper layers, 98.0 x 56.3 mm, 82 parts (0 on the bottom side), 58 nets.

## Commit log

2024-10-24 started schematic work
2024-10-24 end of day work
2024-10-25 mid day progress
2024-10-26 added block diagram
2024-10-26 edited the block diagram
2024-10-26 added block diagram to main
2024-10-26 renamed folders
2024-10-26 renamed documentation folder
2024-10-29 schematic work
2024-11-03 schematic and pcb work
2024-11-04 schematic and pcb layout
2024-11-05 schematic and pcb general layout
2024-11-06 schematic, pcb layout, added mouser shoping cart
2024-11-06 pcb routing
2024-11-07 pcb layout
2024-11-07 edited .gitignore
2024-11-07 PCB routing and DRC fixes
2024-11-08 fixing DRC issues
2024-11-11 schematic release, pcb release
2024-11-12 added block diagram on eng
2024-11-28 working scd40 and sen54 code
2024-11-28 added dps368 reading
2024-12-06 added display functionality, wifi is not working yet
2024-12-09 test
2024-12-11 update case-design photo, removed old block diagram files
2024-12-12 added measurement units to display and live sensor readings
2024-12-13 added defines for selecting displayed variables
2024-12-13 added work in progress data logger script
2024-12-20 added multiple cpp files, testing wifi, fixed user_setup resetting issue
2025-01-05 testing out wifi
2025-01-06 working wifi and value colors
2025-01-06 fixed the value color display, moved the functions to lcd_functions
2025-01-09 added HTTP POST request
2025-01-12 added HTTP post function
2025-01-19 some config changes, auto cleaning interval
2025-01-28 fixed getPressureColor()
2025-01-28 minor comment change, added dashboard-screenshot.png
